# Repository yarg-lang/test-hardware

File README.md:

# test-hardware
Circuit diagrams, etc for Yarg's tests

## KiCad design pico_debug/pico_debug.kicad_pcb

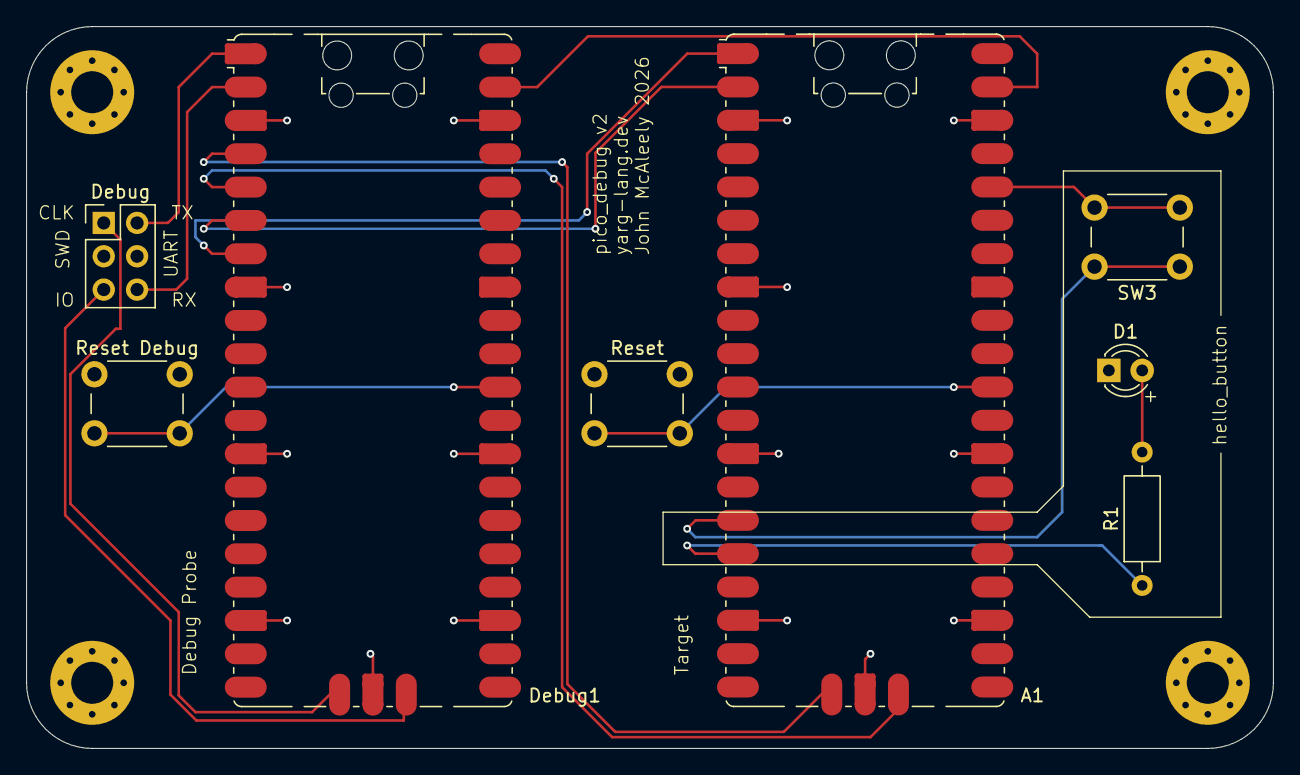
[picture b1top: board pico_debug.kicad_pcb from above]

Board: 2 copper layers, 95.0 x 55.0 mm, 12 parts (0 on the bottom side), 16 nets.

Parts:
A1: RaspberryPi_Pico; RaspberryPi_Pico_SMD_HandSolder
D1: LED; LED_D3.0mm
Debug: Conn_02x03_Counter_Clockwise; PinHeader_2x03_P2.54mm_Vertical
Debug1: RaspberryPi_Pico; RaspberryPi_Pico_SMD_HandSolder
H1, H2, H3, H4: MountingHole; MountingHole_3.2mm_M3_Pad_Via
R1: 220R; R_Axial_DIN0207_L6.3mm_D2.5mm_P10.16mm_Horizontal
Reset: SW_SPST; SW_PUSH_6mm
Reset Debug: SW_SPST; SW_PUSH_6mm
SW3: SW_SPST; SW_PUSH_6mm

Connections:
+3.3V: A1.36 (3V3), SW3.2 (B)
GND: A1.3 (GND_IN), A1.8 (GND), A1.13 (GND), A1.18 (GND), A1.23 (GND), A1.28 (GND), A1.38 (GND), A1.D2 (GND), D1.1 (K), Debug.3, Debug.4, Debug1.3 (GND), Debug1.8 (GND), Debug1.13 (GND), Debug1.18 (GND), Debug1.23 (GND), Debug1.28 (GND), Debug1.38 (GND), Debug1.D2 (GND), Reset.1 (A), Reset Debug.1 (A)
unnamed: A1.1 (UART0_TX), Debug1.7 (GPIO5)
unnamed: A1.2 (UART0_RX), Debug1.6 (GPIO4)
unnamed: A1.15 (GPIO11), SW3.1 (A)
unnamed: A1.16 (GPIO12), R1.1
unnamed: A1.30 (RUN), Reset.2 (B)
unnamed: A1.D1 (SWCLK), Debug1.4 (GPIO2)
unnamed: A1.D3 (SWDIO), Debug1.5 (GPIO3)
unnamed: D1.2 (A), R1.2
unnamed: Debug.2, Debug1.1 (UART0_TX)
unnamed: Debug.6, Debug1.2 (UART0_RX)
unnamed: Debug1.30 (RUN), Reset Debug.2 (B)
unnamed: Debug.1, Debug1.D1 (SWCLK)
unnamed: Debug.5, Debug1.D3 (SWDIO)
VSYS: A1.39 (VSYS_OUT), Debug1.39 (VSYS)

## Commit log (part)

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2025-11-16 Create LICENSE
    Select a permissive hardware licence: CERN OHL v2 Permissive
2025-11-16 initial revision
2025-11-16 remove unwanted pcb
2025-11-16 add kicad .gitignore
2026-06-05 button flash
2026-06-05 pico_debug
2026-06-08 v1 sent to pcbway
